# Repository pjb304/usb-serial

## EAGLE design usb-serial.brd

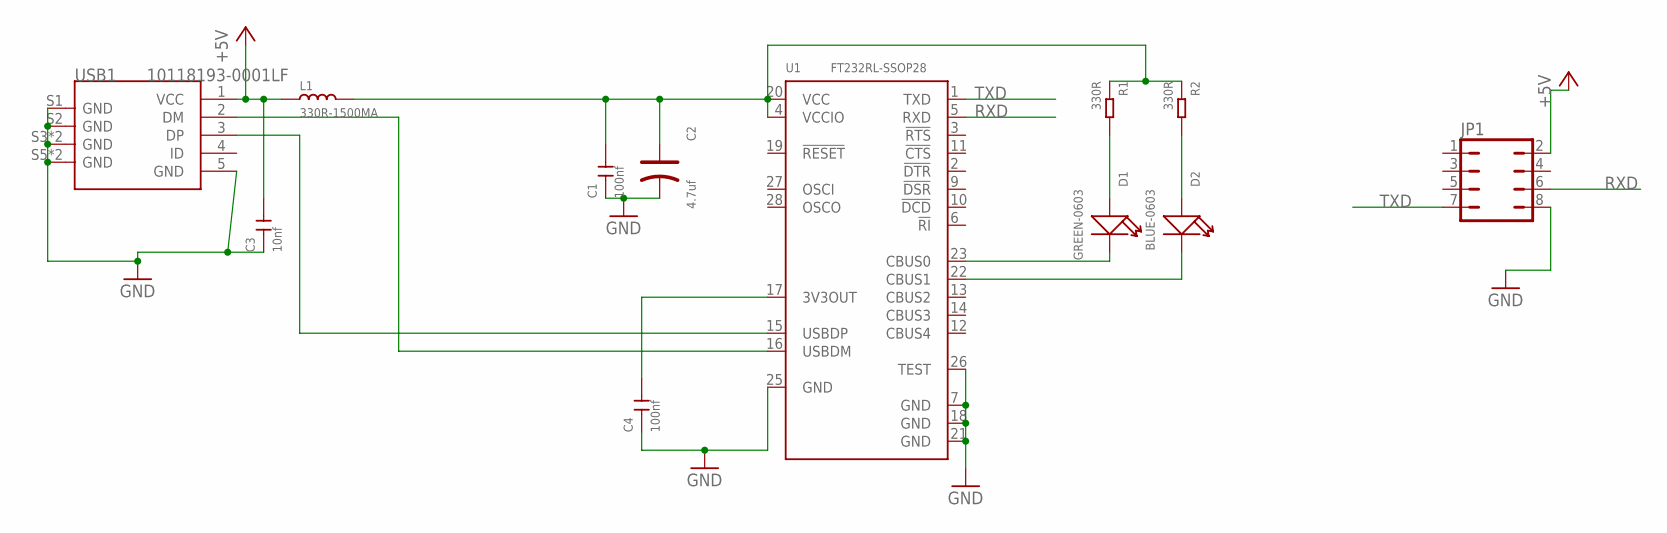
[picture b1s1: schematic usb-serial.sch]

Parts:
C1, C4: 100nf; C0603
C2: 4.7uf; AVX-A
C3: 10nf; C0603
D1: GREEN-0603; LED-0603
D2: BLUE-0603; LED-0603
JP1: JP4Q
L1: 330R-1500MA; L0805
R1, R2: 330R; R0603
U1: FT232RL-SSOP28; SSOP28-0.65-10.2X5.2MM
USB1: 10118193-0001LF; MICRO-USB5+6P-SMD-0.65-B

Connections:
+5V: C3.2, JP1.2, L1.1, USB1.1 (VCC)
GND: C1.1, C2.-, C3.1, C4.1, JP1.8, U1.7 (GND), U1.18 (GND), U1.21 (GND), U1.25 (GND), U1.26 (TEST), USB1.5 (GND), USB1.S1 (GND), USB1.S2 (GND), USB1.S3 (GND), USB1.S4 (GND), USB1.S5 (GND), USB1.S6 (GND)
unnamed: D1.+, R1.2
unnamed: D2.+, R2.2
unnamed: C1.2, C2.+, L1.2, R1.1, R2.1, U1.4 (VCCIO), U1.20 (VCC)
unnamed: U1.15 (USBDP), USB1.3 (DP)
unnamed: U1.16 (USBDM), USB1.2 (DM)
unnamed: C4.2, U1.17 (3V3OUT)
unnamed: D1.-, U1.23 (CBUS0)
unnamed: D2.-, U1.22 (CBUS1)
RXD: JP1.6, U1.5 (RXD)
TXD: JP1.7, U1.1 (TXD)

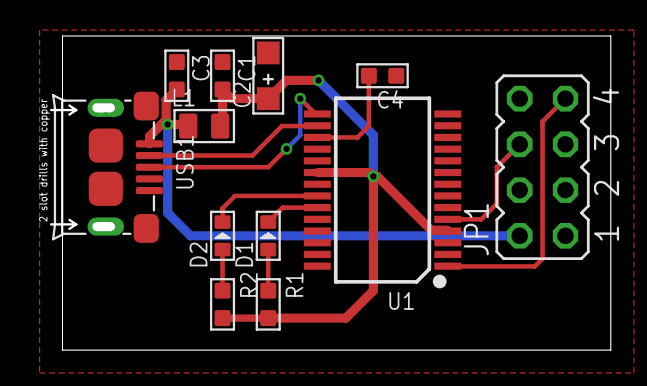
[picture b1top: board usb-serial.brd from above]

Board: 2 copper layers, 31.4 x 16.9 mm, 12 parts (0 on the bottom side), 12 nets.
